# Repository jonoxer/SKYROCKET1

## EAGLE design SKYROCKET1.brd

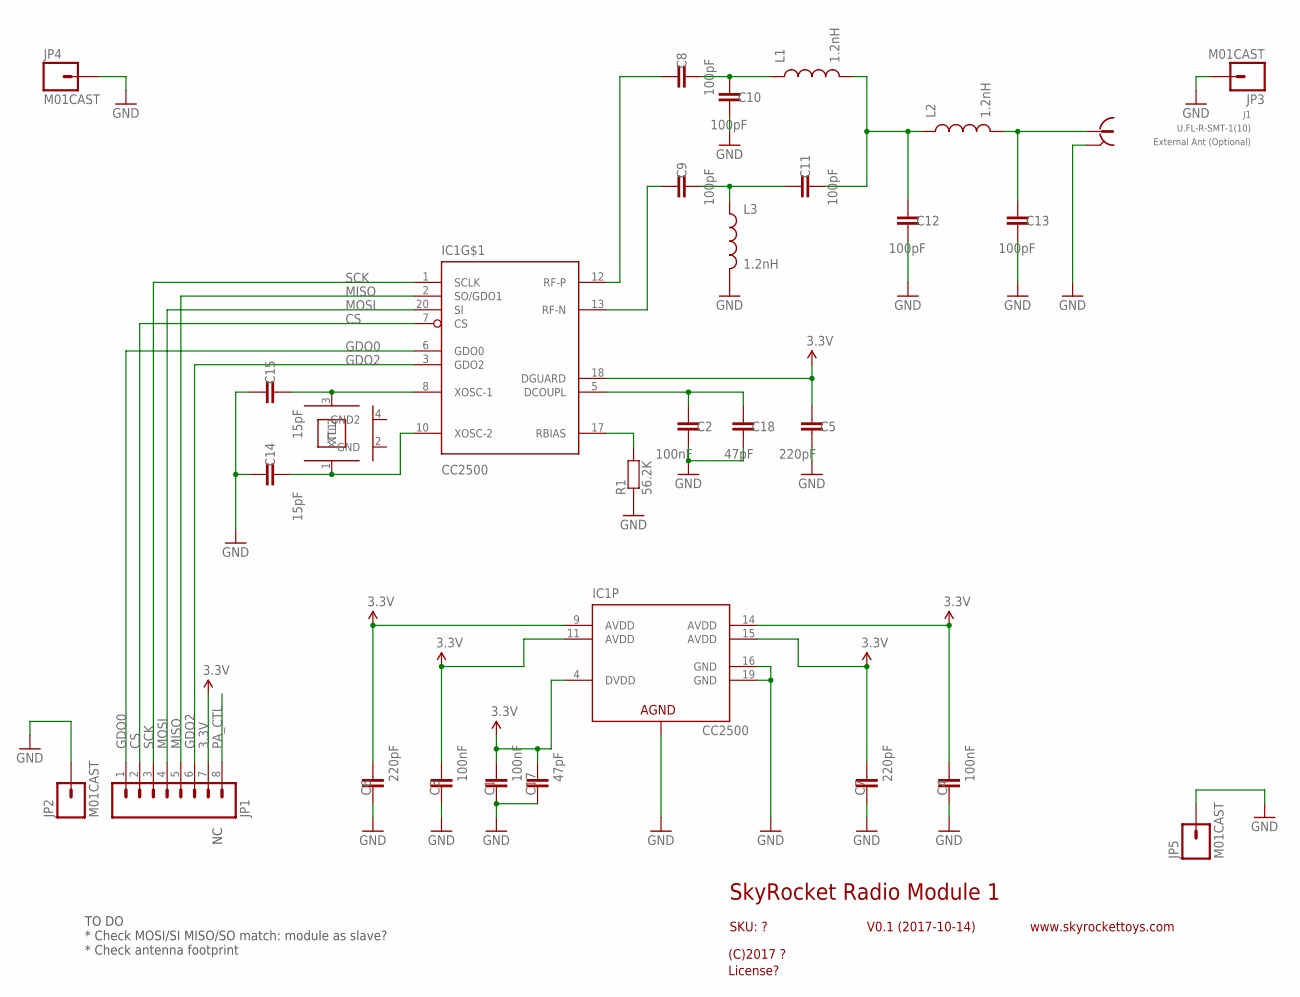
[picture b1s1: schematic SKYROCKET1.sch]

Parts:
C1, C2, C3, C4: 100nF; 0201
C5, C6, C7: 220pF; 0201
C8, C9, C10, C11, C12, C13: 100pF; 0201
C14, C15: 15pF; 0201
C17, C18: 47pF; 0201
IC1: CC2500; QFN50P400X400X90-21N
J1: U.FL-R-SMT-1(10); UFL
JP1: M08CAST; 1X08_CASTELLATED_1.25
JP2, JP3, JP4, JP5: M01CAST; 1X01_CASTELLATED_1.25
L1, L2, L3: 1.2nH; 0603
R1: 56.2K; 0201
XTL1: 26MHz; CRYSTAL-SMD-3X2

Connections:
3.3V: C1.2, C3.2, C4.2, C5.1, C6.2, C7.2, C17.2, IC1.4 (DVDD), IC1.9 (AVDD), IC1.11 (AVDD), IC1.14 (AVDD), IC1.15 (AVDD), IC1.18 (DGUARD), JP1.7
ANT: C13.1, J1.SIG, L2.2
CS: IC1.7 (CS), JP1.2
DCOUPL: C2.1, C18.1, IC1.5 (DCOUPL)
GDO0: IC1.6 (GDO0), JP1.1
GDO2: IC1.3 (GDO2), JP1.6
GND: C1.1, C2.2, C3.1, C4.1, C5.2, C6.1, C7.1, C10.2, C12.2, C13.2, C14.1, C15.1, C17.1, C18.2, IC1.16 (GND), IC1.19 (GND), IC1.21 (AGND), J1.GND, J1.GND@1 (GND), JP2.1, JP3.1, JP4.1, JP5.1, L3.2, R1.1
MISO: IC1.2 (SO/GDO1), JP1.5
MOSI: IC1.20 (SI), JP1.4
unnamed: C8.2, C10.1, L1.1
unnamed: C9.2, C11.1, L3.1
unnamed: IC1.17 (RBIAS), R1.2
unnamed: C11.2, C12.1, L1.2, L2.1
unnamed: C9.1, IC1.13 (RF-N)
unnamed: C8.1, IC1.12 (RF-P)
unnamed: C15.2, IC1.8 (XOSC-1), XTL1.3 (XTL2)
unnamed: C14.2, IC1.10 (XOSC-2), XTL1.1 (XTL1)
PA_CTL: JP1.8
SCK: IC1.1 (SCLK), JP1.3

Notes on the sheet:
SkyRocket Radio Module 1
V0.1 (2017-10-14)
SKU: ?
(C)2017 ?
License?
www.skyrockettoys.com
TO DO * Check MOSI/SI MISO/SO match: module as slave? * Check antenna footprint

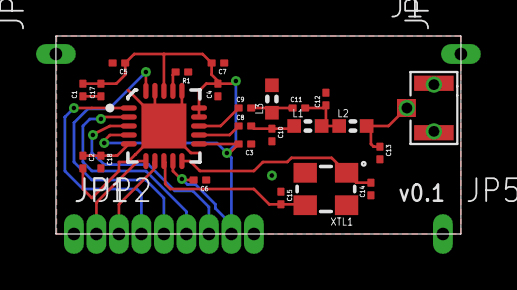
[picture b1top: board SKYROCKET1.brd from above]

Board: 2 copper layers, 22.5 x 11.0 mm, 29 parts (0 on the bottom side), 18 nets.

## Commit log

2019-04-24 Import old project files
